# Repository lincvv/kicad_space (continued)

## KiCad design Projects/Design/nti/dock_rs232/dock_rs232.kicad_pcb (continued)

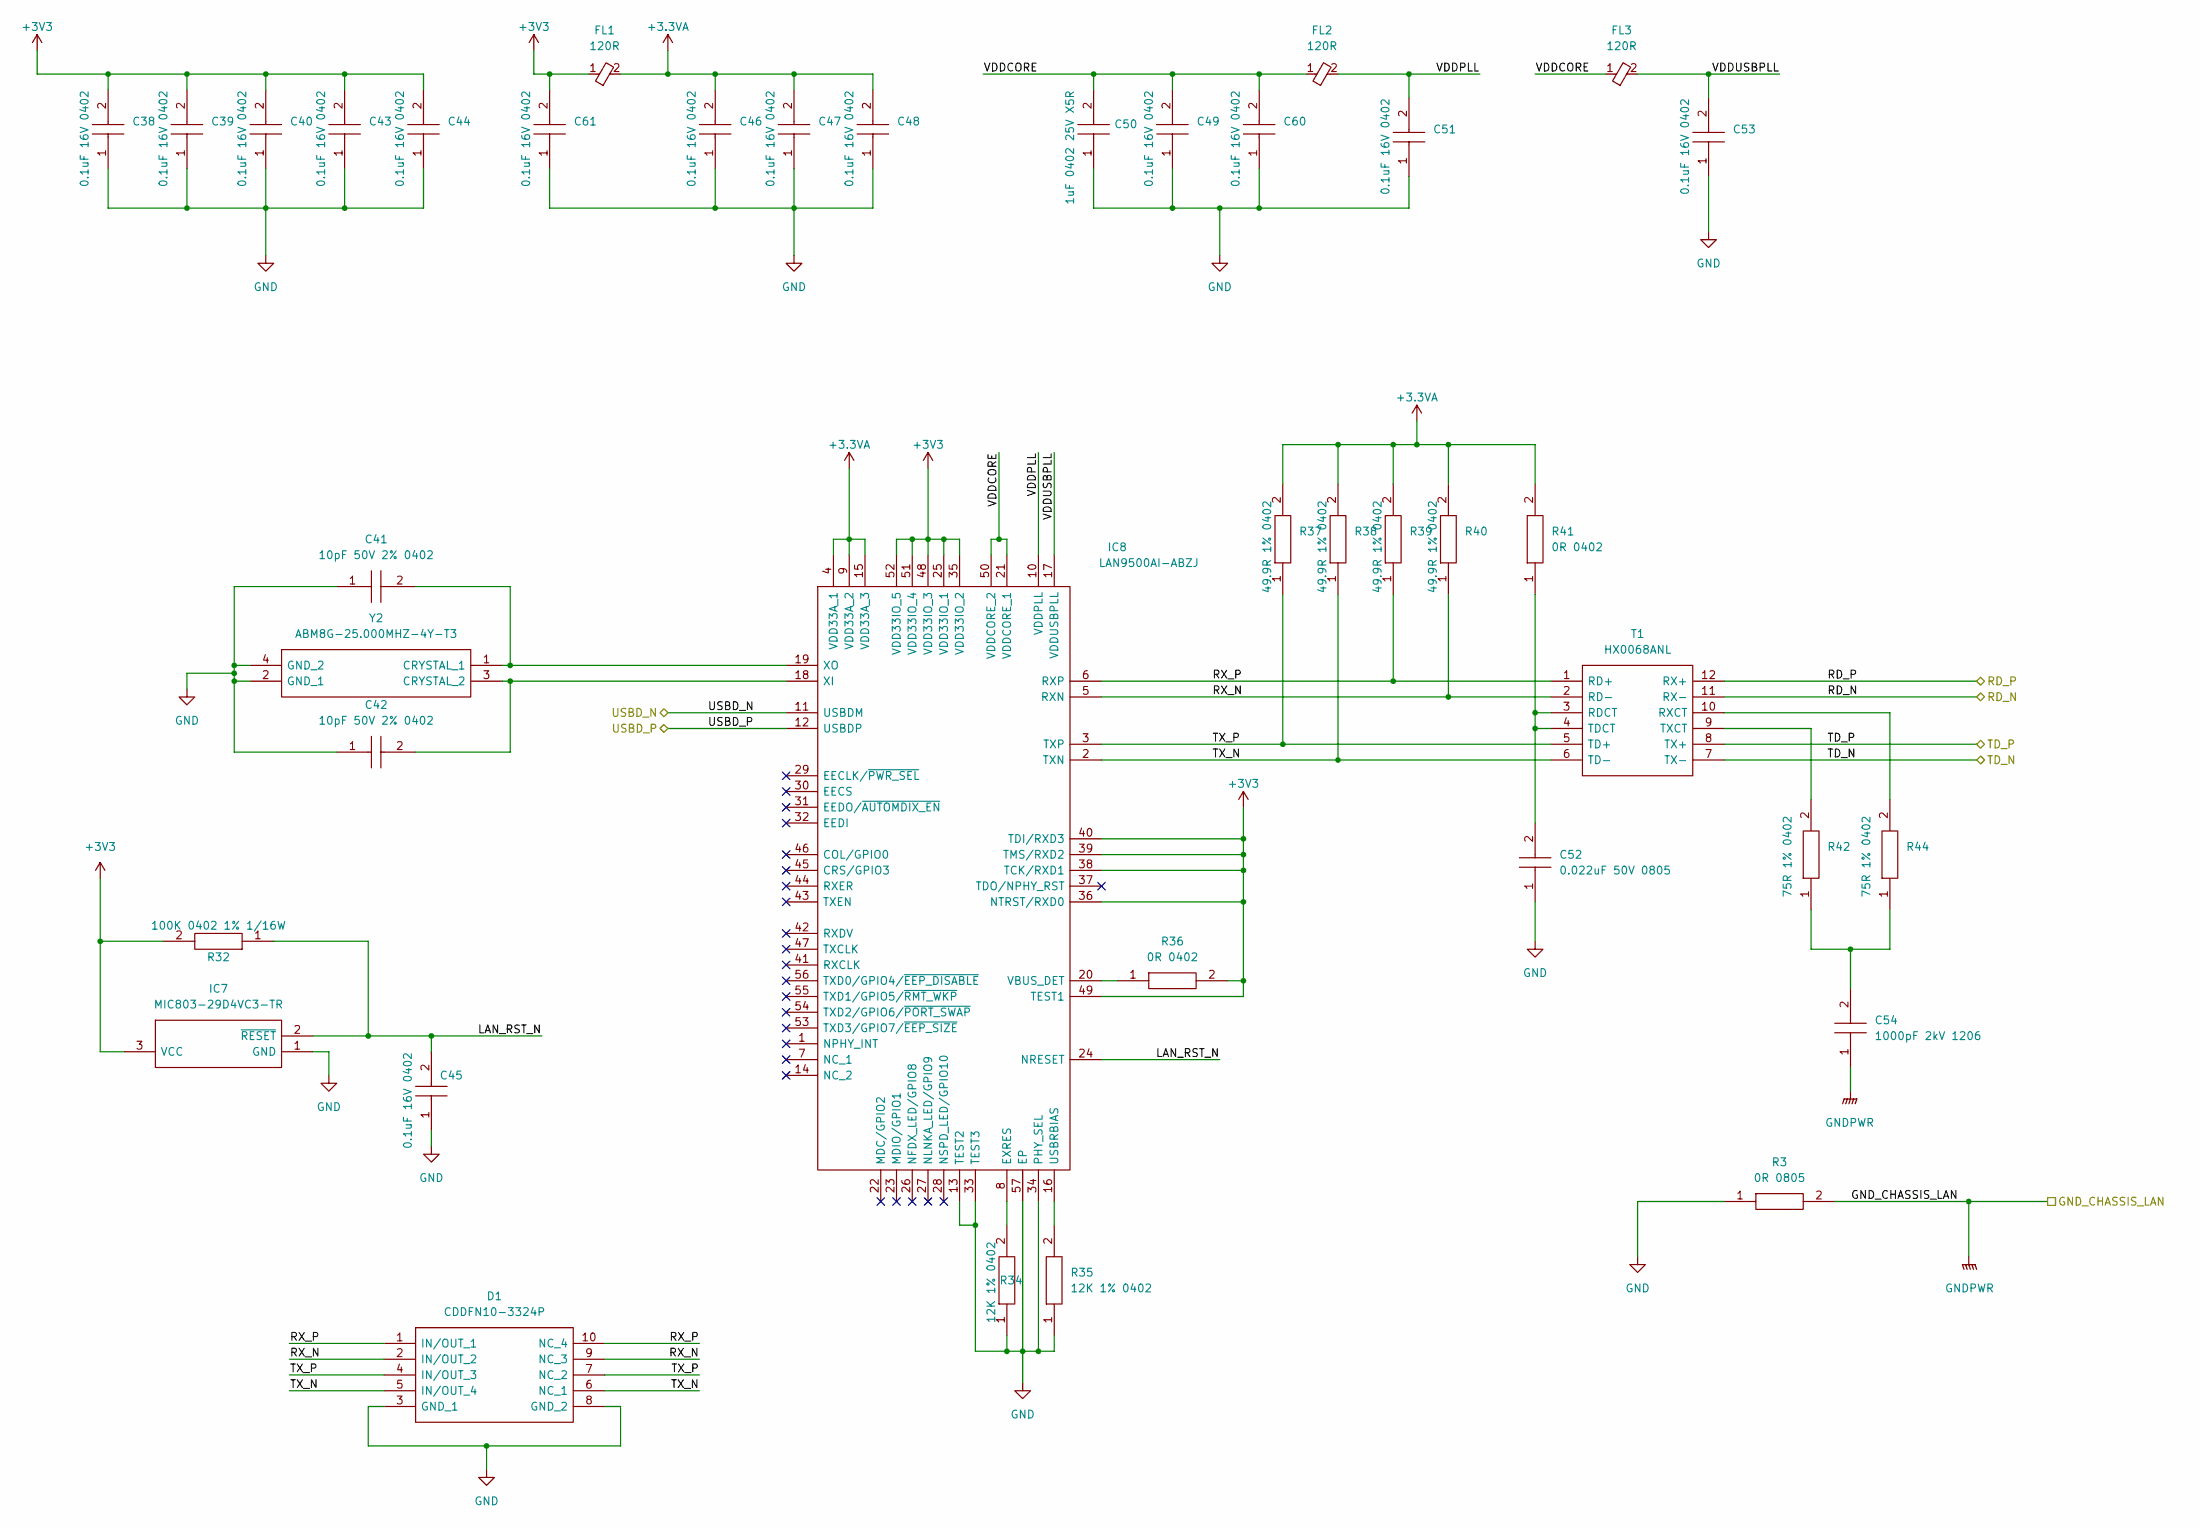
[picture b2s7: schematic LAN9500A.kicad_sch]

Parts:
C38, C39, C40, C43, C44, C45, C46, C47, C48, C49, C51, C53, C60, C61: 0.1uF 16V 0402; C_0402_1005Metric; Manufacturer_Part_Number GRM155R71C104KA88D; Mouser Part Number N/A
C41, C42: 10pF 50V 2% 0402; C_0402_1005Metric; Manufacturer_Part_Number GJM1555C1H100GB01D; Mouser Part Number 81-GJM1555C1H100GB01
C50: 1uF 0402 25V X5R; C_0402_1005Metric; Manufacturer_Part_Number GRM155R61E105KA12D; Mouser Part Number 81-GRM155R61E105KA2D
C52: 0.022uF 50V 0805; C_0805_2012Metric; Manufacturer_Part_Number AC0805KRX7R9BB223; Mouser Part Number 603-AC805KRX7R9BB223
C54: 1000pF 2kV 1206; C_1206_3216Metric; Manufacturer_Part_Number C1206C102KGRACAUTO; Mouser Part Number 80-C1206C102KGRAUTO
D1: CDDFN10-3324P; CDDFN103324P; Manufacturer_Part_Number CDDFN10-3324P; Mouser Part Number 652-CDDFN10-3324P
FL1, FL2, FL3: 120R; L_0603_1608Metric; Manufacturer_Part_Number BLM18AG121SN1D; Mouser Part Number 81-BLM11A121S
IC7: MIC803-29D4VC3-TR; SOT65P210X100-3N; Manufacturer_Part_Number MIC803-29D4VC3-TR; Mouser Part Number 998-MIC803-29D4VC3TR
IC8: LAN9500AI-ABZJ; QFN50P800X800X100-57N-D; Manufacturer_Part_Number LAN9500AI-ABZJ; Mouser Part Number 886-LAN9500AI-ABZJ
R3: 0R 0805; R_0805_2012Metric; Manufacturer_Part_Number ERJ-6GEY0R00V; Mouser Part Number 667-ERJ-6GEY0R00V
R32: 100K 0402 1% 1/16W; R_0402_1005Metric; Manufacturer_Part_Number SFR01MZPF1003; Mouser Part Number 755-SFR01MZPF1003
R34, R35: 12K 1% 0402; R_0402_1005Metric; Manufacturer_Part_Number ERJ-U02F1202X
R36, R41: 0R 0402; R_0402_1005Metric; Manufacturer_Part_Number CR0402-J/-000GLF; Mouser Part Number 652-CR0402-J/-000GLF
R37, R38, R39, R40: 49.9R 1% 0402; R_0402_1005Metric; Manufacturer_Part_Number ERJ-2RKF49R9X; Mouser Part Number 667-ERJ-2RKF49R9X
R42, R44: 75R 1% 0402; R_0402_1005Metric; Manufacturer_Part_Number ERJ-2RKF75R0X; Mouser Part Number 667-ERJ-2RKF75R0X
T1: HX0068ANL; Manufacturer_Part_Number HX0068ANL; Mouser Part Number 673-HX0068ANL
Y2: ABM8G-25.000MHZ-4Y-T3; ABM8G48000MHZ18D2YT; Manufacturer_Part_Number ABM8G-25.000MHZ-4Y-T3; Mouser Part Number 815-ABM8G-25-4YT3

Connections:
+3.3VA: C46.2, C47.2, C48.2, FL1.2, IC8.4 (VDD33A_1), IC8.9 (VDD33A_2), IC8.15 (VDD33A_3), R37.2, R38.2, R39.2, R40.2, R41.2
+3V3: C38.2, C39.2, C40.2, C43.2, C44.2, C61.2, FL1.1, IC7.3 (VCC), IC8.25 (VDD33IO_1), IC8.35 (VDD33IO_2), IC8.36 (NTRST/RXD0), IC8.38 (TCK/RXD1), IC8.39 (TMS/RXD2), IC8.40 (TDI/RXD3), IC8.48 (VDD33IO_3), IC8.49 (TEST1), IC8.51 (VDD33IO_4), IC8.52 (VDD33IO_5), R32.2, R36.2; also elsewhere on the board
/USB LAN/LAN_RST_N: C45.2, IC7.2 (~RESET), IC8.24 (NRESET), R32.1
/USB LAN/RD_N: T1.11 (RX-); also elsewhere on the board
/USB LAN/RD_P: T1.12 (RX+); also elsewhere on the board
/USB LAN/RX_N: D1.2 (IN/OUT_2), D1.9 (NC_3), IC8.5 (RXN), R40.1, T1.2 (RD-)
/USB LAN/RX_P: D1.1 (IN/OUT_1), D1.10 (NC_4), IC8.6 (RXP), R39.1, T1.1 (RD+)
/USB LAN/TD_N: T1.7 (TX-); also elsewhere on the board
/USB LAN/TD_P: T1.8 (TX+); also elsewhere on the board
/USB LAN/TX_N: D1.5 (IN/OUT_4), D1.6 (NC_1), IC8.2 (TXN), R38.1, T1.6 (TD-)
/USB LAN/TX_P: D1.4 (IN/OUT_3), D1.7 (NC_2), IC8.3 (TXP), R37.1, T1.5 (TD+)
/USB LAN/VDDCORE: C49.2, C50.2, C60.2, FL2.1, FL3.1, IC8.21 (VDDCORE_1), IC8.50 (VDDCORE_2)
/USB LAN/VDDPLL: C51.2, FL2.2, IC8.10 (VDDPLL)
/USB LAN/VDDUSBPLL: C53.2, FL3.2, IC8.17 (VDDUSBPLL)
/USBDN1_N: IC8.11 (USBDM); also elsewhere on the board
/USBDN1_P: IC8.12 (USBDP); also elsewhere on the board
GND: C38.1, C39.1, C40.1, C41.1, C42.1, C43.1, C44.1, C45.1, C46.1, C47.1, C48.1, C49.1, C50.1, C51.1, C52.1, C53.1, C60.1, C61.1, D1.3 (GND_1), D1.8 (GND_2), IC7.1 (GND), IC8.13 (TEST2), IC8.33 (TEST3), IC8.34 (PHY_SEL), IC8.57 (EP), R3.1, R34.1, R35.1, Y2.2 (GND_1), Y2.4 (GND_2); also elsewhere on the board
GNDPWR: C54.1, R3.2; also elsewhere on the board
unnamed: C41.2, IC8.19 (XO), Y2.1 (CRYSTAL_1)
unnamed: C42.2, IC8.18 (XI), Y2.3 (CRYSTAL_2)
unnamed: C52.2, R41.1, T1.3 (RDCT), T1.4 (TDCT)
unnamed: C54.2, R42.1, R44.1
unnamed: IC8.8 (EXRES), R34.2
unnamed: IC8.16 (USBRBIAS), R35.2
unnamed: IC8.20 (VBUS_DET), R36.1
unnamed: R42.2, T1.9 (TXCT)
unnamed: R44.2, T1.10 (RXCT)

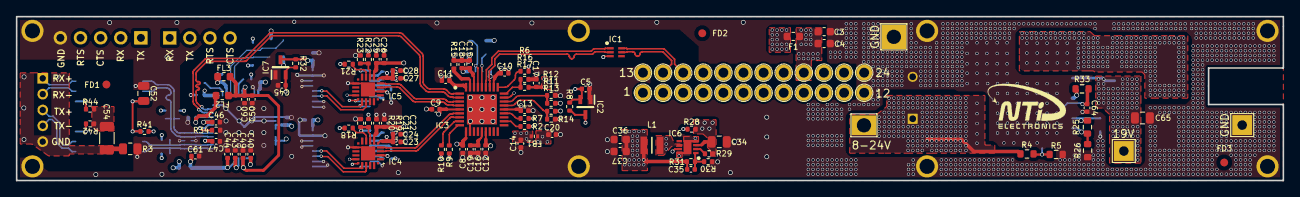
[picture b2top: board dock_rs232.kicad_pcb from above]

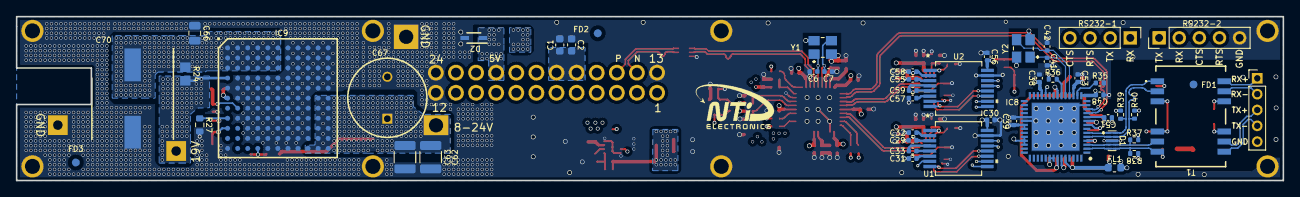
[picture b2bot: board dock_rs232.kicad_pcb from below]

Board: 6 copper layers, 160.0 x 20.7 mm, 169 parts (50 on the bottom side), 99 nets.

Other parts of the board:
*: 19V; TestPoint_THTPad_2.5x2.5mm_Drill1.2mm
FD1, FD1#2, FD2, FD2#2, FD3, FD3#2: Fiducial_1mm_Mask2mm

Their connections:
GND: *.1; also elsewhere on the board

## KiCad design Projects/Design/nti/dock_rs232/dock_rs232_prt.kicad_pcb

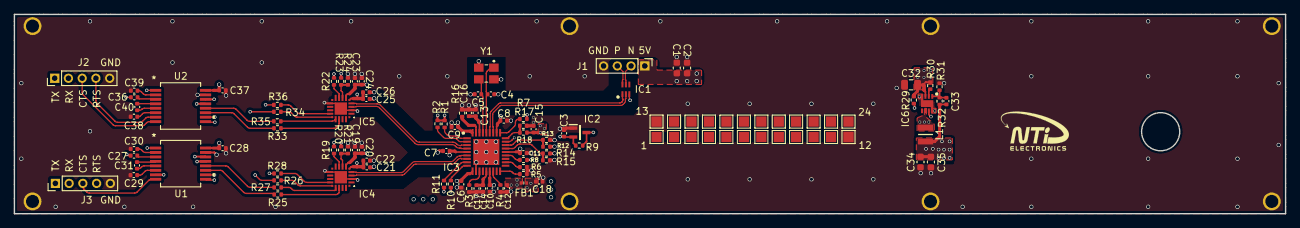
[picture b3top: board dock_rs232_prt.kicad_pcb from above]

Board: 4 copper layers, 185.0 x 29.0 mm, 114 parts (0 on the bottom side), 77 nets.

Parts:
C1: 10nF 50V; C_0603_1608Metric
C2: 0.1uF 50V; C_0603_1608Metric
C3, C6, C7, C8, C9, C10, C11, C19, C21, C23, C25: 0.1uF 16V 0402; C_0402_1005Metric
C4, C5: 10pF 2%; C_0402_1005Metric
C12, C18: 4.7uF 6.3V; C_0402_1005Metric
C13, C14: 0.01uF 10V; C_0402_1005Metric
C15: 1uF 0402 25V X5R; C_0402_1005Metric
C16, C17: 0.1uF 16V; C_0402_1005Metric
C20, C22, C24, C26: 4.7uF 6V3 0402; C_0402_1005Metric
C27, C28, C29, C30, C31, C36, C37, C38, C39, C40: 0.1uF 0402 X7R; C_0402_1005Metric
C32: 10uF 10V 0805; C_0805_2012Metric
C33: 22pF 50V 0402 10%; C_0402_1005Metric
C34, C35: 22uF 6.3V 0603 20%; C_0603_1608Metric
FB1: BLM15PG100SZ1D; NFZ15SG152SN10B
IC1: ECMF02-2AMX6; SON50P150X170X55-6N-D
IC2: MIC803-29D2VC3-TR; SOT65P210X100-3N
IC3: USB2514B_M2; QFN50P600X600X100-37N-D
IC4, IC5: CP2102N-A02-GQFN20; CP2102NA02GQFN20
IC6: AP3441SHE-7B; SON50P201X201X60-9N-D
J1: Screw_Terminal_01x04; PinHeader_1x04_P2.00mm_Vertical
J2, J3: Screw_Terminal_01x05; PinHeader_1x05_P2.00mm_Vertical
L1: 2.2uH 2.2A; DFE2HCAH1R0MJ0L
P1, P2, P3, P4, P5, P6, P7, P8, P9, P11: NC; TestPoint_Pad_1.5x1.5mm
P10: NC'; TestPoint_Pad_1.5x1.5mm
P12: GPIO; TestPoint_Pad_1.5x1.5mm
P13: USB3_TX_N; TestPoint_Pad_1.5x1.5mm
P14: USB3_TX_P; TestPoint_Pad_1.5x1.5mm
P15: USB3_RX_P; TestPoint_Pad_1.5x1.5mm
P16: USB3_RX_N; TestPoint_Pad_1.5x1.5mm
P17, P18: GND; TestPoint_Pad_1.5x1.5mm
P19, P20: GHARGE_19V; TestPoint_Pad_1.5x1.5mm
P21: +5V_DOCK; TestPoint_Pad_1.5x1.5mm
P22: USB2__N; TestPoint_Pad_1.5x1.5mm
P23: USB2_P; TestPoint_Pad_1.5x1.5mm
P24: DOCK_IN_DET; TestPoint_Pad_1.5x1.5mm
R1, R2, R7, R8, R10, R11, R12: 10K 0402 1%; R_0402_1005Metric
R3, R4, R5, R6, R9, R13, R14, R15, R17, R18, R30: 100K 0402 1% 1/16W; R_0402_1005Metric
R16: 12K 1%; R_0402_1005Metric
R19, R22: 1K 0402; R_0402_1005Metric
R20, R23: 22K6 0402; R_0402_1005Metric
R21, R24: 47K 0402; R_0402_1005Metric
R25, R26, R27, R28, R33, R34, R35, R36: 0R 0402; R_0402_1005Metric
R29: 10K 0402 1% 1/16W; R_0402_1005Metric
R31: 95.3K 0402 1% 1/10W; R_0402_1005Metric
R32: 430K 0402 1% 1/10W; R_0402_1005Metric
U1, U2: MAX3232MDBREP
Y1: ABM8G-24.000MHZ-4Y-T3; ABM8G48000MHZ18D2YT

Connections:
+3V3: C10.2, C11.2, C18.2, C28.2, C33.2, C34.2, C35.2, C37.2, FB1.2, IC2.3 (VCC), IC3.15 (VDD33_1), IC3.23 (VDD33_2), L1.2, R1.2, R2.2, R7.2, R8.2, R9.2, R10.2, R11.2, R12.2, R14.1, R32.2, U1.16 (VCC), U2.16 (VCC)
/PWR_3V3/FB: C33.1, IC6.1 (FB), R31.2, R32.1
/PWR_3V3/LX: IC6.6 (LX), L1.1
/RS232_P1_CTS: J2.3, U2.8 (RIN2)
/RS232_P1_RTS: J2.4, U2.7 (DOUT2)
/RS232_P1_RXD: J2.2, U2.13 (RIN1)
/RS232_P1_TXD: J2.1, U2.14 (DOUT1)
/RS232_P2_CTS: J3.3, U1.8 (RIN2)
/RS232_P2_RTS: J3.4, U1.7 (DOUT2)
/RS232_P2_RXD: J3.2, U1.13 (RIN1)
/RS232_P2_TXD: J3.1, U1.14 (DOUT1)
/USB2UP_N: IC1.5 (D-), J1.2
/USB2UP_P: IC1.6 (D+), J1.3
/USB HUB/BC_EN1: IC3.12 (PRTPWR1/BC_EN1), R3.2
/USB HUB/BC_EN2: IC3.16 (PRTPWR2/BC_EN2), R4.2
/USB HUB/BC_EN3: IC3.18 (PRTPWR3/BC_EN3), R5.2
/USB HUB/BC_EN4: IC3.20 (PRTPWR4/BC_EN4), R6.2
/USB HUB/CFG_SEL0: IC3.24 (SCL/SMBCLK/CFG_SEL0), R14.2, R15.1
/USB HUB/CFG_SEL1: IC3.25 (HS_IND/CFG_SEL1), R12.1, R13.1
/USB HUB/CRFILT: C14.2, C17.2, IC3.14 (CRFILT)
/USB HUB/HUB_RST_N: C3.2, IC2.2 (~RESET), IC3.26 (RESET_N), R9.1
/USB HUB/NON_REM0: IC3.28 (SUSP_IND/LOCAL_PWR/NON_REM0), R7.1
/USB HUB/NON_REM1: IC3.22 (SDA/SMBDATA/NONREM1), R8.1
/USB HUB/PLLFILT: C13.2, C16.2, IC3.34 (PLLFILT)
/USB HUB/USBDN4_N: IC3.8 (USBDM_DN4/PRT_DIS_M4), R11.1
/USB HUB/USBDN4_P: IC3.9 (USBDP_DN4/PRT_DIS_P4), R10.1
/USB HUB/USBUP_N: IC1.2 (D_2), IC3.30 (USBDM_UP)
/USB HUB/USBUP_P: IC1.1 (D_1), IC3.31 (USBDP_UP)
/USB HUB/VBUS_DET: IC3.27 (VBUS_DET), R17.1, R18.2
/USB HUB/VDDA33: C6.2, C7.2, C8.2, C9.2, C12.2, FB1.1, IC3.5 (VDDA33_1), IC3.10 (VDDA33_2), IC3.29 (VDDA33_3), IC3.36 (VDDA33_4)
/USB SERIAL_1/CTS: IC5.15 (CTS), R36.1
/USB SERIAL_1/RTS: IC5.16 (RTS), R34.1
/USB SERIAL_1/RXD: IC5.17 (RXD), R35.1
/USB SERIAL_1/TXD: IC5.18 (TXD), R33.1
/USB SERIAL_1/VDD: C25.2, C26.2, IC5.6 (VDD), R22.2
/USB SERIAL_2/CTS: IC4.15 (CTS), R28.1
/USB SERIAL_2/RTS: IC4.16 (RTS), R26.1
/USB SERIAL_2/RXD: IC4.17 (RXD), R27.1
/USB SERIAL_2/TXD: IC4.18 (TXD), R25.1
/USB SERIAL_2/VDD: C21.2, C22.2, IC4.6 (VDD), R19.2
/USBDN1_N: IC3.1 (USBDM_DN1/PRT_DIS_M1), R1.1
/USBDN1_P: IC3.2 (USBDP_DN1/PRT_DIS_P1), R2.1
/USBDN2_N: IC3.3 (USBDM_DN2/PRT_DIS_M2), IC5.5 (D-)
/USBDN2_P: IC3.4 (USBDP_DN2/PRT_DIS_P2), IC5.4 (D+)
/USBDN3_N: IC3.6 (USBDM_DN3/PRT_DIS_M3), IC4.5 (D-)
/USBDN3_P: IC3.7 (USBDP_DN3/PRT_DIS_P3), IC4.4 (D+)
/driver 232_1/DIN1: R33.2, U2.11 (DIN1)
/driver 232_1/DIN2: R34.2, U2.10 (DIN2)
/driver 232_1/ROUT1: R35.2, U2.12 (ROUT1)
/driver 232_1/ROUT2: R36.2, U2.9 (ROUT2)
/driver 232_2/DIN1: R25.2, U1.11 (DIN1)
/driver 232_2/DIN2: R26.2, U1.10 (DIN2)
/driver 232_2/ROUT1: R27.2, U1.12 (ROUT1)
/driver 232_2/ROUT2: R28.2, U1.9 (ROUT2)
GND: C1.1, C2.1, C3.1, C4.1, C5.1, C6.1, C7.1, C8.1, C9.1, C10.1, C11.1, C12.1, C13.1, C14.1, C15.1, C16.1, C17.1, C18.1, C19.1, C20.1, C21.1, C22.1, C23.1, C24.1, C25.1, C26.1, C28.1, C29.1, C30.1, C32.1, C34.1, C35.1, C37.1, C38.1, C39.1, IC1.3 (GND), IC2.1 (GND), IC3.11 (TEST), IC3.37 (EP), IC4.3 (GND_1), IC4.12 (GND_2), IC4.21 (EP_GND), IC5.3 (GND_1), IC5.12 (GND_2), IC5.21 (EP_GND), IC6.4 (PGND), IC6.8 (SGND), IC6.9 (EP), J1.4, J2.5, J3.5, P17.1, P18.1, R3.1, R4.1, R5.1, R6.1, R13.2, R15.2, R16.1, R17.2, R21.1, R24.1, R31.1, U1.15 (GND), U2.15 (GND), Y1.2 (GND_1), Y1.4 (GND_2)
unnamed: C4.2, IC3.32 (XTALOUT), Y1.1 (CRYSTAL_1)
unnamed: C5.2, IC3.33 (XTALIN/CLKIN), Y1.3 (CRYSTAL_2)
unnamed: C27.1, U1.3 (C1-)
unnamed: C27.2, U1.1 (C1+)
unnamed: C29.2, U1.6 (V-)
unnamed: C30.2, U1.2 (V+)
unnamed: C31.1, U1.4 (C2+)
unnamed: C31.2, U1.5 (C2-)
unnamed: C36.1, U2.3 (C1-)
unnamed: C36.2, U2.1 (C1+)
unnamed: C38.2, U2.6 (V-)
unnamed: C39.2, U2.2 (V+)
unnamed: C40.1, U2.4 (C2+)
unnamed: C40.2, U2.5 (C2-)
unnamed: IC3.35 (RBIAS), R16.2
unnamed: IC4.8 (VBUS), R20.1, R21.2
unnamed: IC4.9 (RSTB), R19.1
unnamed: IC5.8 (VBUS), R23.1, R24.2
unnamed: IC5.9 (RSTB), R22.1
unnamed: IC6.2 (PG), R30.2
unnamed: IC6.7 (EN), R29.2
VBUS_UP: C1.2, C2.2, C15.2, C19.2, C20.2, C23.2, C24.2, C32.2, IC4.7 (VREGIN), IC5.7 (VREGIN), IC6.3 (VIN), J1.1, R18.1, R20.2, R23.2, R29.1, R30.1
